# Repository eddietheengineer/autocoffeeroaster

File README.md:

# Automatic Coffee Roaster
Convert an original Poppery popcorn popper in to an automatic coffee roaster

    -Closed loop temperature control throughout entire roast
    -Customize rate of temperature rise through each phase of roast
    -AC Phase Control for both blower fan and heater

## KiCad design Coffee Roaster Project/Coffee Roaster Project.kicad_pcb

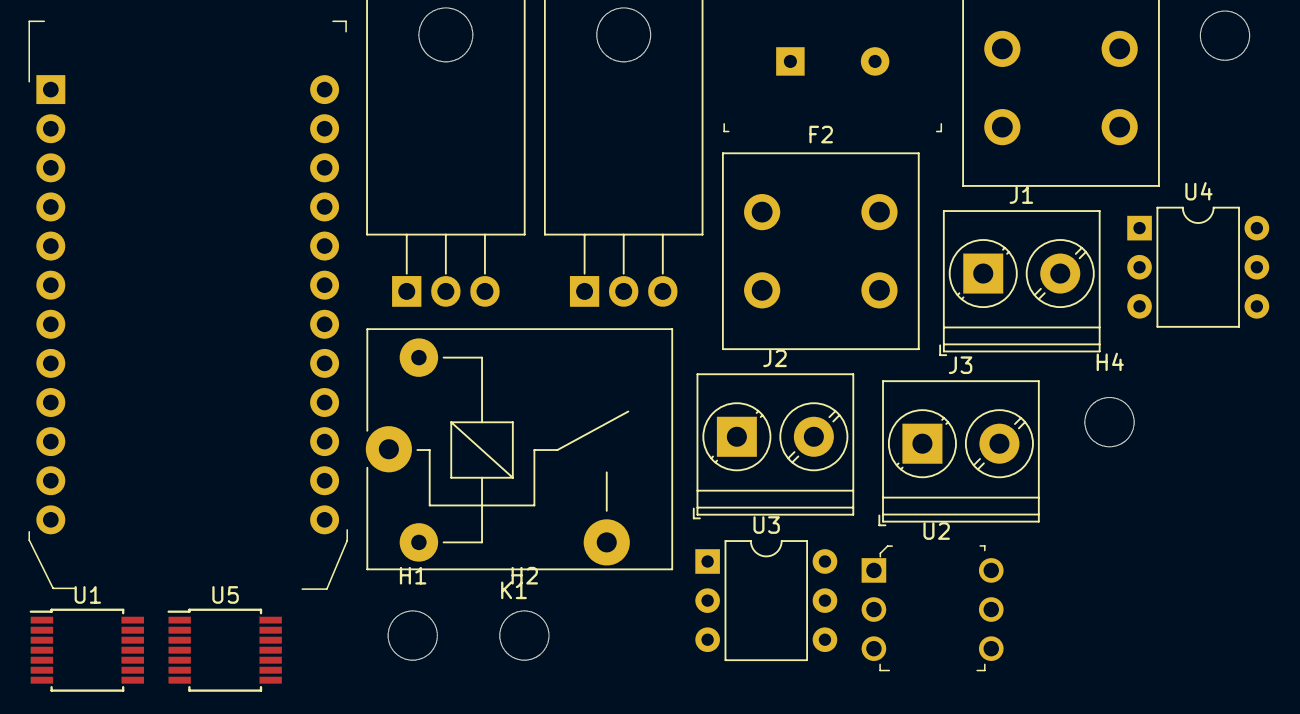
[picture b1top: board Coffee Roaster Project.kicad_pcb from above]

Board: 2 copper layers, 19 parts (0 on the bottom side), 20 nets, no tracks yet.

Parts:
A1: PHOTONH; Particle_Photon
D1, D2: Q_TRIAC_A1A2G; TO-220-3_Horizontal_TabDown
F1, F2: Fuse; Fuseholder_Cylinder-5x20mm_Schurter_FPG4_Vertical_Closed
F3: DFP10112; TCO_5.5mm_Radial
H1, H2, H3, H4: MountingHole; MountingHole_3.2mm_M3_ISO7380
J1, J2, J3: Screw_Terminal_01x02; TerminalBlock_Phoenix_PT-1,5-2-5.0-H_1x02_P5.00mm_Horizontal
K1: SANYOU_SRD_Form_A; Relay_SPST_SANYOU_SRD_Series_Form_A
U1, U5: MAX31856; TSSOP-14_4.4x5mm_P0.65mm
U2: 4N25; DIP-6_W7.62mm
U3, U4: MOC3011M; DIP-6_W7.62mm

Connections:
+3V3: A1.24, U1.5, U1.8, U5.5, U5.8
A0: A1.12, U1.9
A1: A1.11, U5.9
A2: A1.10, U1.10, U5.10
A3: A1.9, U1.11, U5.11
A4: A1.8, U1.12, U5.12
D0: A1.13, U2.5
D1: A1.14, K1.5
GND: A1.2, K1.2, U1.1, U1.14, U2.4, U3.2, U4.2, U5.1, U5.14
N: D1.1, D2.1, F2.1
unnamed: A1.1, J1.2
unnamed: A1.21, J1.1
unnamed: J2.1, U1.2, U1.3
unnamed: J2.2, U1.4
unnamed: J3.1, U5.2, U5.3
unnamed: J3.2, U5.4
unnamed: D1.2, U3.6
unnamed: D2.2, U4.6
unnamed: F1.1, K1.3
unnamed: F1.2, F3.2

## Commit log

2019-09-01 Initial code commit
2020-02-22 Add initial schematic
    initial schematic, needs more work
